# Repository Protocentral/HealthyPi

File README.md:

# This repository is OBSOLETE. Please visit https://github.com/Protocentral/protocentral-healthypi-v3 for the current version. 

# ProtoCentral HealthyPi HAT for Raspberry Pi

This HAT for Raspberry Pi 3 / 2 includes vital patient monitoring including ECG, respiration, pulse oximetry and features options to add blood pressure and body temperature sensing.

This is a one-of-a-kind, all-in-one HAT for your Raspberry Pi 2 /3 computer. Just plug it into the Raspberry Pi, install the graphical visualisation software and start using. Unlike available shields and breakouts that we carry for Arduino, this board combines all the functions into a a single board.

Repository Contents
-------------------
* **/firmware** - Atmel studio  and aduino example sketches.
* **/Hardware** - All Eagle design files (.brd, .sch)
* **/extras** - includes the datasheet
* **/gui** - HealthyPi GUI for Raspberry Pi and PC
* **/docs** - Additional Documentation

Getting Started (On Raspberry Pi):
----------------------------------

Mount ProtoCentral's Healthy PI Hat carefully onto the Raspberry Pi Board's GPIO Pins. And connect this setup with the Raspberry Pi's Display or HDMI Monitor. The Hat communicate with Raspberry Pi using UART interface. Connect the ECG electrodes and SPO2 Probe to the ProtoCentral's Healthy PI Hat.

It's now easy to get started with our brand-new installation script. Just follow the following steps on your Raspberry Pi.

To start, open up the terminal window (Menu -> Accessories -> Terminal) on Raspbian running on your Raspberry Pi:

In the terminal window, type the following lines. 

```bash
curl -sS http://pi.protocentral.com/pi.sh | sudo bash
```

It really is as simple as that !!

This code will install all the required overlays, configuration and application files to get the Healthy Pi up and running.

After the script reboots, you should be able to see the GUI display on the screen

### This completes the install!

If the above script does not work for you and would like to do a manual installation or would like to customize the code, check out [Advanced HealthyPi] (/docs/advanced-healthypi.md).

Using the HealthyPi GUI on Windows, MacOS and Linux
---------------------------------------------------
The HealthyPi board now streams the same data on the on-board USB port. This allows you to get the same data that goes to the Raspberry Pi, now on your desktop PC as well. 

Java 8 is required on all platforms for running the processing-based GUI application. You can download Java for your platform from the following link.

[https://java.com/en/download/](https://java.com/en/download/)

#### Installing drivers (only for Windows)

HealthyPi uses the same drivers as an Arduino Zero. Once plugged in to the USB port, the device would be recognized as an "Unknown Device". You can locate the device is the Windows Device Manager and manually install the drivers provided in the "drivers" folder in the Windows Executable ZIP archive provided.

MacOS and Linux do not need any drivers to be installed.

### Processing GUI Installation

Download the zip file containing the executable files from the following links for 32-bit/64-bit Windows. If you do not know if you have a 64-bit or 32-bit computer, please download the 32-bit version.

* [Windows 32-bit Executable (ZIP)](https://github.com/Protocentral/HealthyPi/releases/download/v0.2/healthypi_gui_win32.zip)
* [Windows 64-bit Executable (ZIP)](https://github.com/Protocentral/HealthyPi/releases/download/v0.2/healthypi_gui_win64.zip)
* [MacOS Executable (ZIP)](https://github.com/Protocentral/HealthyPi/releases/download/v0.2/healthypi_gui_macos.zip)
* [Linux 32-bit Executable (ZIP)](https://github.com/Protocentral/HealthyPi/releases/download/v0.2/healthypi_gui_linux32.zip)
* [Linux 64-bit Executable (ZIP)](https://github.com/Protocentral/HealthyPi/releases/download/v0.2/healthypi_gui_linux64.zip)

Simply download the appropriate file for your operating system, unzip the contents and run the executable program contained in it. 

Programming the on-board SAMD21 microcontroller
--------------------------------------------------

HealthyPi now supports programming using Arduino ! 

If you wish to program your own code on the HealthyPi board, check out [Modifying and recompiling HealthyPi Firmware](/docs/recompiling-firmware.md).

Connecting the ECG Electrodes
------------------------------
 A 3-electrode cable along with a standard stereo jack is provided along with the shield to connect the electrodes to the  board. 
 The other side of the electrode connector would connect to snap-on electrodes attached to the body. For testing purposes,    you can use an ECG simulator to provide inputs to the board. 

 Warning:
 When connecting the electodes to the body, it is safer to disconnect the mains power source to the Arduino. For example, if  you are using the Arduino along with a laptop, disconnecting the battery charger from the laptop would be a safe option.
 
Placing the Electrodes on the body
---------------------------------

License Information
===================

This product is open source! Both, our hardware and software are open source and licensed under the following licenses:

Hardware
---------

**All hardware is released under [Creative Commons Share-alike 4.0 International](http://creativecommons.org/licenses/by-sa/4.0/).**

Software
--------

**All software is released under the MIT License(http://opensource.org/licenses/MIT).**

Please check [*LICENSE.md*](LICENSE.md) for detailed license descriptions.

THE SOFTWARE IS PROVIDED "AS IS", WITHOUT WARRANTY OF ANY KIND, EXPRESS OR
IMPLIED, INCLUDING BUT NOT LIMITED TO THE WARRANTIES OF MERCHANTABILITY,
FITNESS FOR A PARTICULAR PURPOSE AND NONINFRINGEMENT. IN NO EVENT SHALL THE
AUTHORS OR COPYRIGHT HOLDERS BE LIABLE FOR ANY CLAIM, DAMAGES OR OTHER
LIABILITY, WHETHER IN AN ACTION OF CONTRACT, TORT OR OTHERWISE, ARISING FROM,
OUT OF OR IN CONNECTION WITH THE SOFTWARE OR THE USE OR OTHER DEALINGS IN THE
SOFTWARE.

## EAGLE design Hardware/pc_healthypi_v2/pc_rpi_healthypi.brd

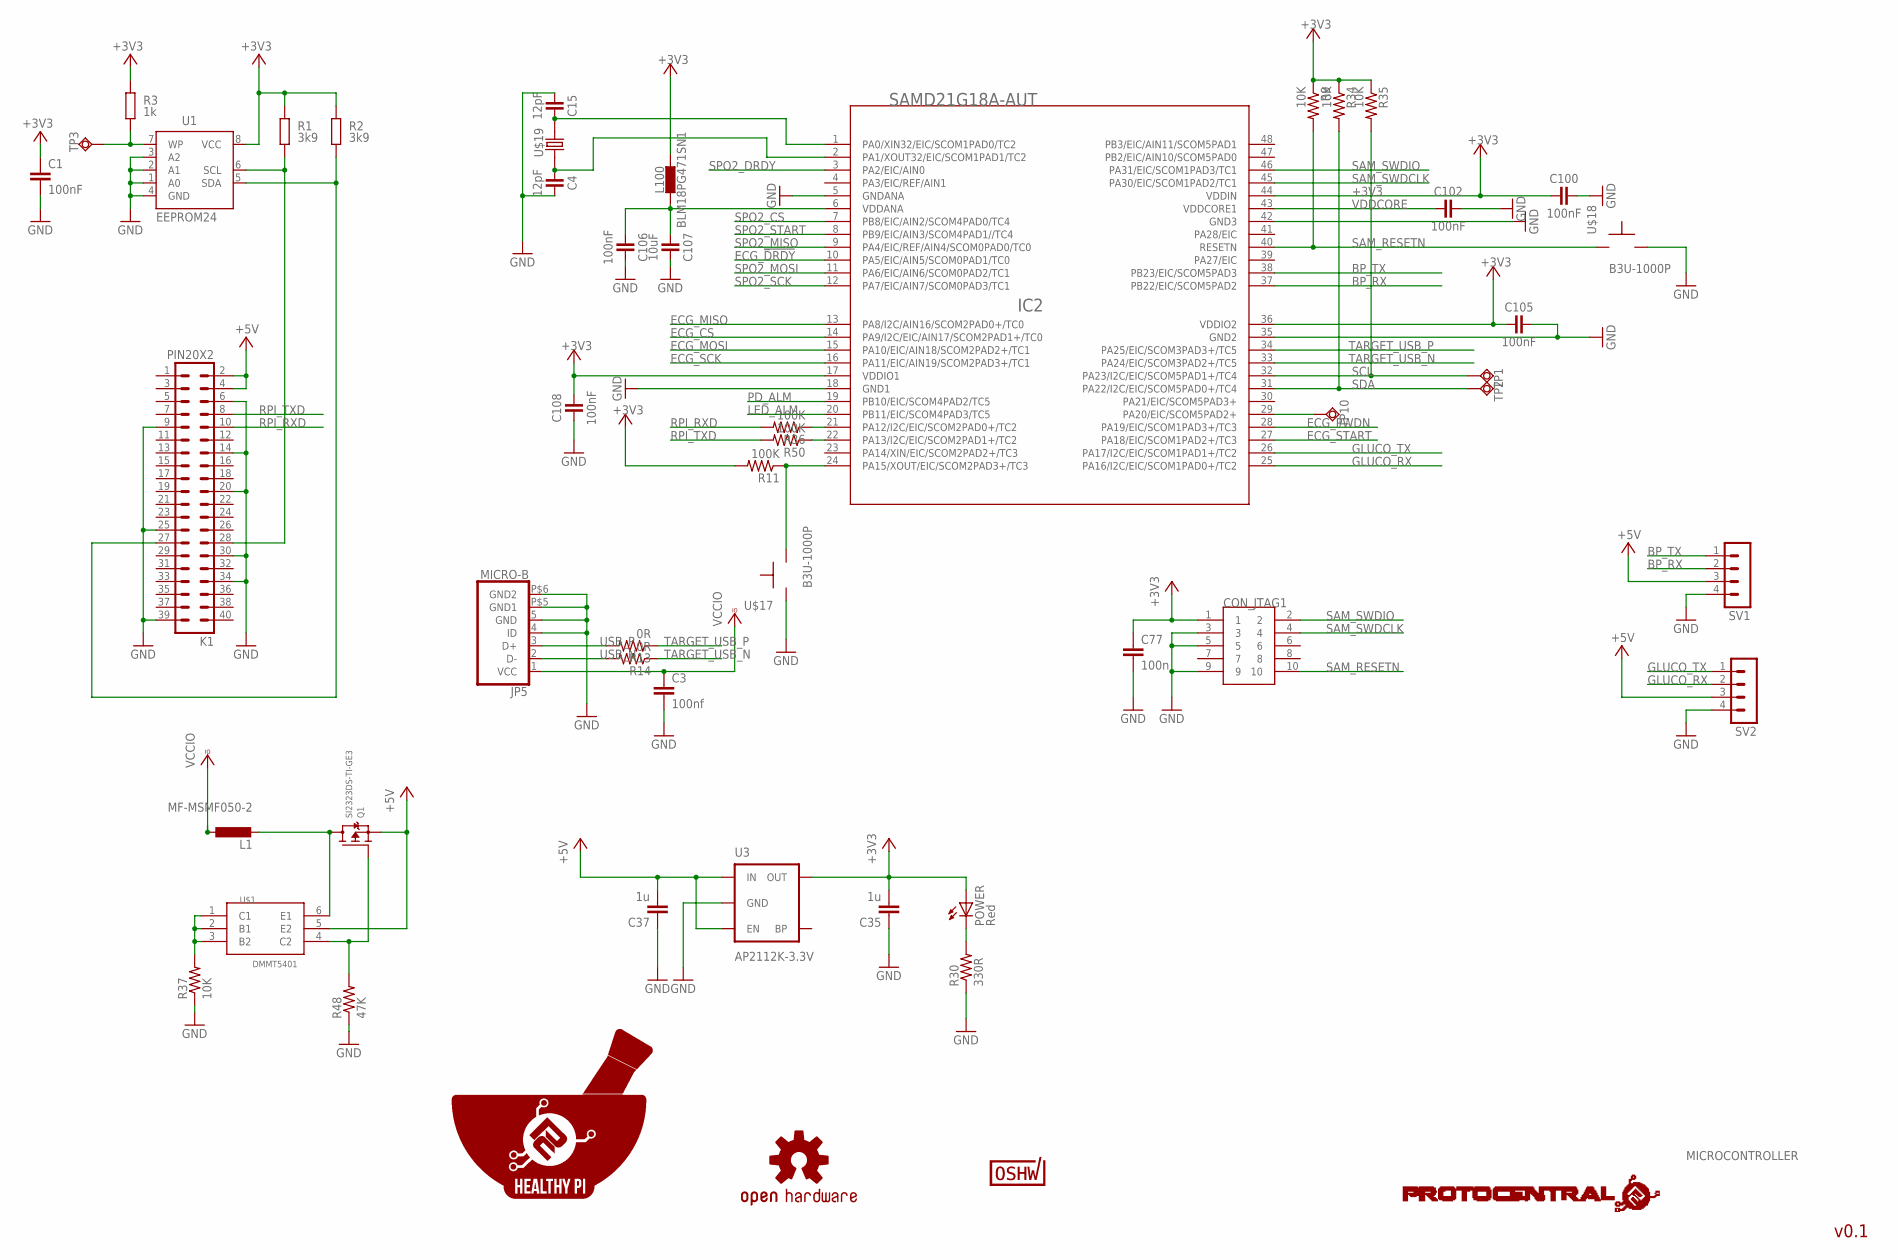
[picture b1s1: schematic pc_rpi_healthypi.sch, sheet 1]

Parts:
C1: 100nF; C0805K
C3: 100nf; C0402
C4, C15: 12pF; C0402
C35, C37: 1u; C0402
C77: 100n; C0805
C100, C102, C105, C106, C108: 100nF; C0805
C107: 10uF; C0805
CON_JTAG1: HDR-SMT-50MIL/5X2
IC2: SAMD21G18A-AUT; TQFP48
JP5: MICRO-B
K1: PIN20X2; PIN_20X2
L1: MF-MSMF050-2; L1812
L100: BLM18PG471SN1; C0603
POWER: Red; CHIPLED_0603
Q1: SI2323DS-TI-GE3; SOT23-R
R1, R2: 3k9; M0805; TOLERANCE 5%
R3: 1k; M0805; TOLERANCE 5%
R9, R34, R35, R37: 10K; R0805
R11: 100K; R0805
R13, R14: 0R; R0402
R30: 330R; R0402
R36, R50: 100K; R0402
R48: 47K; R0805
SV1, SV2: MA04-1
TP1, TP2, TP3, TP10: TPSQB1,27; B1,27
U1: EEPROM24; SOIC8
U3: AP2112K-3.3V; SOT23-5
U$1: DMMT5401; SOT26
U$5: OSHW-LOGOM; OSHW-LOGO-M
U$6: PROTY_LOGO_WITH_TEXT; PROTY_WITH_TEXT
U$13: CERT-SMALL; CERT-SMALL-SILK
U$15: HEALTHYPI
U$17, U$18: B3U-1000P
U$19: ECS-X-34B; ECX-31B

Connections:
+3V3: C1.1, C35.2, C77.1, C100.1, C105.1, C108.2, CON_JTAG1.1, IC2.17 (VDDIO1), IC2.36 (VDDIO2), IC2.44 (VDDIN), L100.2, POWER.A, R1.2, R2.2, R3.2, R9.1, R11.2, R34.1, R35.1, U1.8 (VCC), U3.5 (OUT); also elsewhere on the board
+5V: C37.2, K1.2, K1.4, Q1.2 (S), SV1.3, SV2.3, U3.1 (IN), U3.3 (EN), U$1.5 (E2)
BP_RX: IC2.37 (PB22/EIC/SCOM5PAD2), SV1.2
BP_TX: IC2.38 (PB23/EIC/SCOM5PAD3), SV1.1
ECG_!DRDY: IC2.10 (PA5/EIC/AIN5/SCOM0PAD1/TC0); also elsewhere on the board
ECG_CS: IC2.14 (PA9/I2C/EIC/AIN17/SCOM2PAD1+/TC0); also elsewhere on the board
ECG_MISO: IC2.13 (PA8/I2C/AIN16/SCOM2PAD0+/TC0); also elsewhere on the board
ECG_MOSI: IC2.15 (PA10/EIC/AIN18/SCOM2PAD2+/TC1); also elsewhere on the board
ECG_PWDN: IC2.28 (PA19/EIC/SCOM1PAD3+/TC3); also elsewhere on the board
ECG_SCK: IC2.16 (PA11/EIC/AIN19/SCOM2PAD3+/TC1); also elsewhere on the board
ECG_START: IC2.27 (PA18/EIC/SCOM1PAD2+/TC3); also elsewhere on the board
GLUCO_RX: IC2.25 (PA16/I2C/EIC/SCOM1PAD0+/TC2), SV2.2
GLUCO_TX: IC2.26 (PA17/I2C/EIC/SCOM1PAD1+/TC2), SV2.1
GND: C1.2, C3.2, C4.2, C15.1, C35.1, C37.1, C77.2, C100.2, C102.2, C105.2, C106.2, C107.2, C108.1, CON_JTAG1.3, CON_JTAG1.5, CON_JTAG1.9, IC2.5 (GNDANA), IC2.18 (GND1), IC2.35 (GND2), IC2.42 (GND3), JP5.4 (ID), JP5.5 (GND), JP5.P$5 (GND1), JP5.P$6 (GND2), K1.6, K1.9, K1.14, K1.20, K1.25, K1.30, K1.34, K1.39, R30.1, R37.1, R48.1, SV1.4, SV2.4, U1.1 (A0), U1.2 (A1), U1.3 (A2), U1.4 (GND), U3.2 (GND), U$17.P$1, U$18.P$2; also elsewhere on the board
LED_ALM: IC2.20 (PB11/EIC/SCOM4PAD3/TC5); also elsewhere on the board
unnamed: K1.28, R1.1, U1.6 (SCL)
unnamed: K1.27, R2.1, U1.5 (SDA)
unnamed: R3.1, TP3.TP, U1.7 (WP)
unnamed: C15.2, IC2.1 (PA0/XIN32/EIC/SCOM1PAD0/TC2), U$19.P$2 (2)
unnamed: C106.1, C107.1, IC2.6 (VDDANA), L100.1
unnamed: POWER.C, R30.2
unnamed: C4.1, IC2.2 (PA1/XOUT32/EIC/SCOM1PAD1/TC2), U$19.P$1 (1)
unnamed: IC2.21 (PA12/I2C/EIC/SCOM2PAD0+/TC2), R36.1
unnamed: IC2.22 (PA13/I2C/EIC/SCOM2PAD1+/TC2), R50.1
unnamed: IC2.24 (PA15/XOUT/EIC/SCOM2PAD3+/TC3), R11.1, U$17.P$2
unnamed: IC2.29 (PA20/EIC/SCOM5PAD2+), TP10.TP
unnamed: R37.2, U$1.1 (C1), U$1.2 (B1), U$1.3 (B2)
unnamed: Q1.1 (G), R48.2, U$1.4 (C2)
unnamed: L1.2, Q1.3 (D), U$1.6 (E1)
PD_ALM: IC2.19 (PB10/EIC/SCOM4PAD2/TC5); also elsewhere on the board
RPI_RXD: K1.10, R36.2
RPI_TXD: K1.8, R50.2
SAM_RESETN: CON_JTAG1.10, IC2.40 (RESETN), R9.2, U$18.P$1
SAM_SWDCLK: CON_JTAG1.4, IC2.45 (PA30/EIC/SCOM1PAD2/TC1)
SAM_SWDIO: CON_JTAG1.2, IC2.46 (PA31/EIC/SCOM1PAD3/TC1)
SCL: IC2.32 (PA23/I2C/EIC/SCOM5PAD1+/TC4), R35.2, TP1.TP
SDA: IC2.31 (PA22/I2C/EIC/SCOM5PAD0+/TC4), R34.2, TP2.TP
SPO2_CS: IC2.7 (PB8/EIC/AIN2/SCOM4PAD0/TC4); also elsewhere on the board
SPO2_DRDY: IC2.3 (PA2/EIC/AIN0); also elsewhere on the board
SPO2_MISO: IC2.9 (PA4/EIC/REF/AIN4/SCOM0PAD0/TC0); also elsewhere on the board
SPO2_MOSI: IC2.11 (PA6/EIC/AIN6/SCOM0PAD2/TC1); also elsewhere on the board
SPO2_SCK: IC2.12 (PA7/EIC/AIN7/SCOM0PAD3/TC1); also elsewhere on the board
SPO2_START: IC2.8 (PB9/EIC/AIN3/SCOM4PAD1//TC4); also elsewhere on the board
TARGET_USB_N: IC2.33 (PA24/EIC/SCOM3PAD2+/TC5), R14.1
TARGET_USB_P: IC2.34 (PA25/EIC/SCOM3PAD3+/TC5), R13.1
USB_N: JP5.2 (D-), R14.2
USB_P: JP5.3 (D+), R13.2
VCCIO: C3.1, JP5.1 (VCC), L1.1
VDDCORE: C102.1, IC2.43 (VDDCORE1)

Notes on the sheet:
v0.1
MICROCONTROLLER

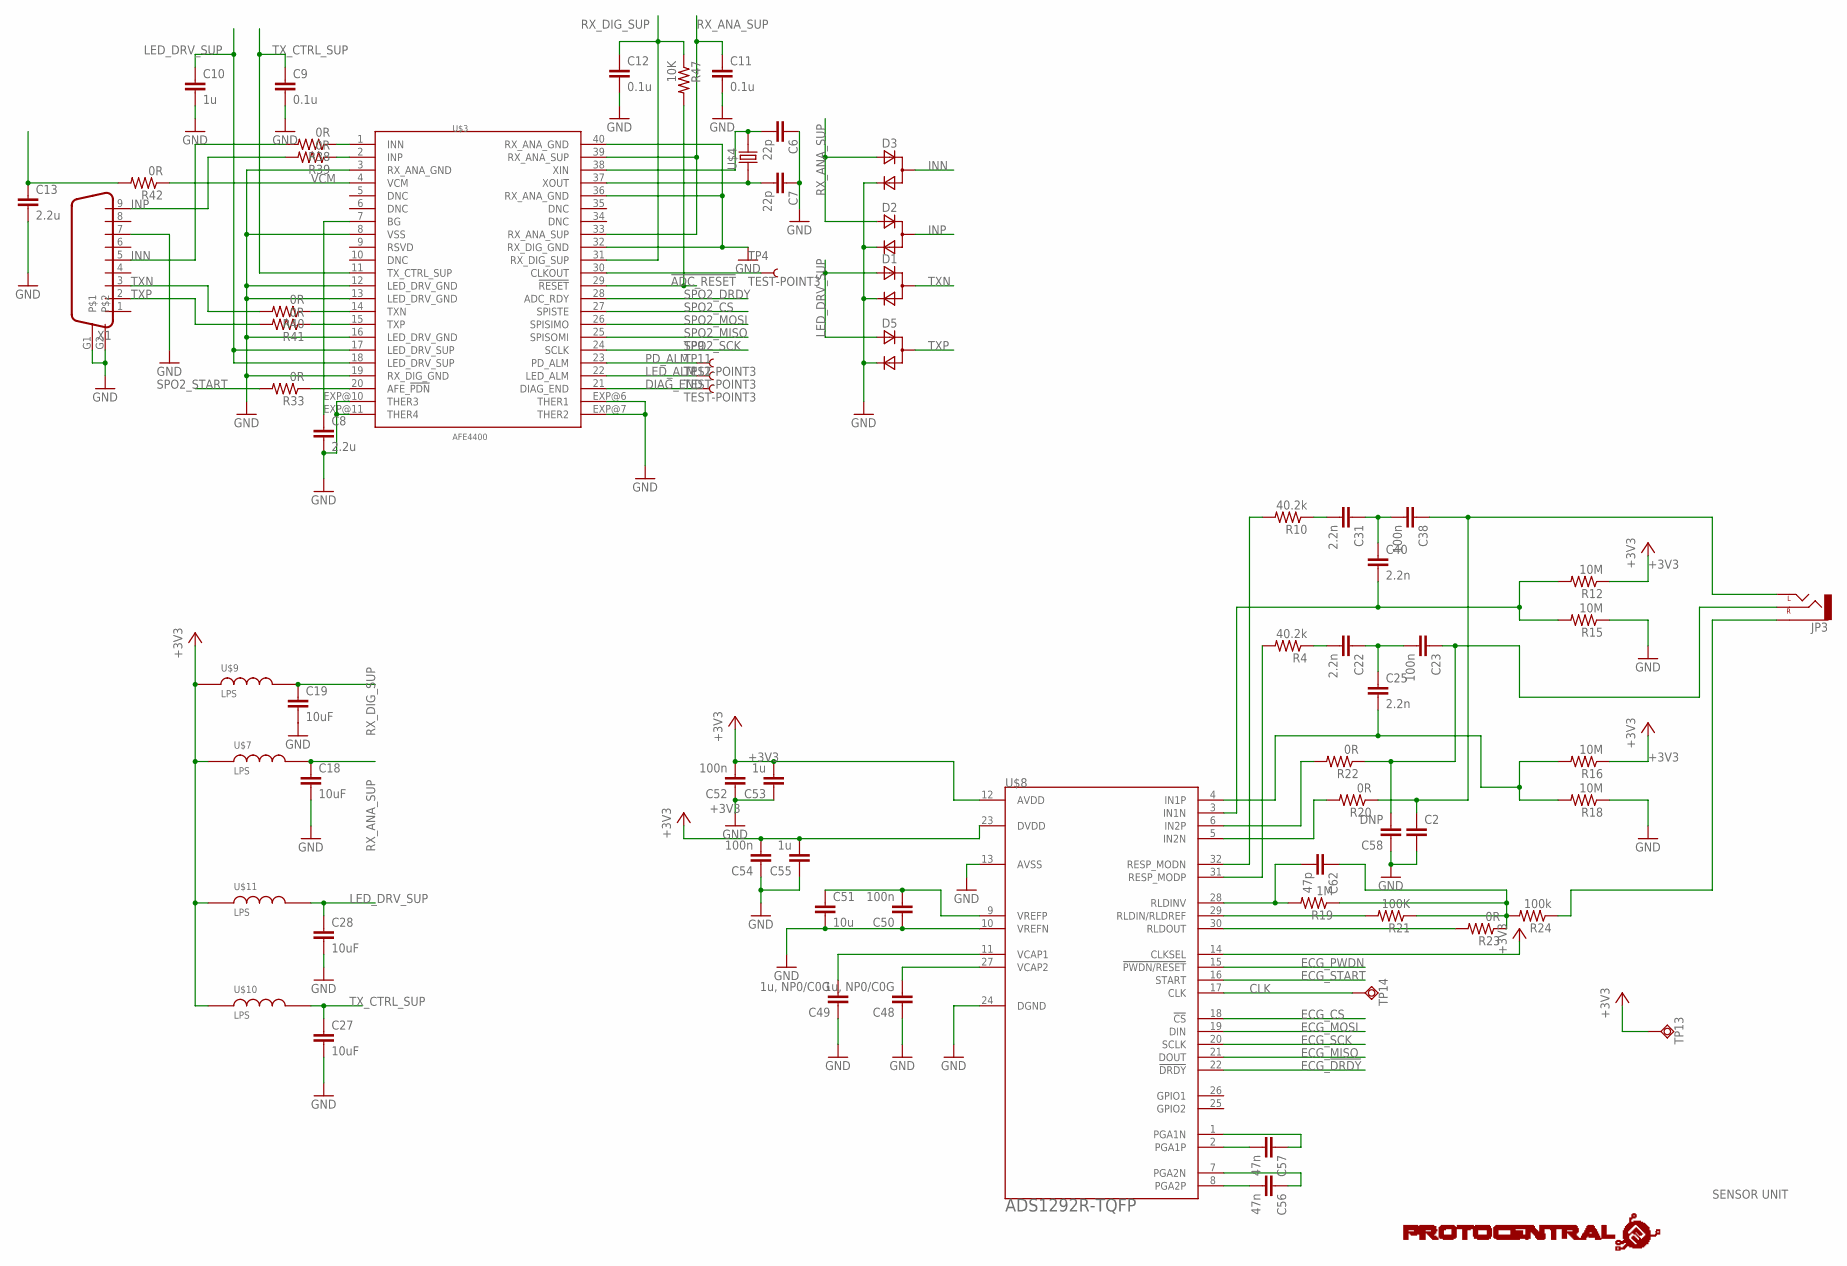
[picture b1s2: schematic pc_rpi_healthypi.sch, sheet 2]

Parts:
C2: C-EUC0402; C0402
C6, C7: 22p; C0402
C8, C13: 2.2u; C0402
C9, C11, C12: 0.1u; C0402
C10: 1u; C0805
C18, C19, C27, C28: 10uF; C0805
C22, C25, C31, C40: 2.2n; C0402
C23, C38, C50, C52, C54: 100n; C0402
C48, C49: 1u, NP0/C0G; C0402
C51: 10u; C0603
C53, C55: 1u; C0402
C56, C57: 47n; C0402
C58: DNP; C0402
C62: 47p; C0402
D1, D2, D3, D5: D_ACACSOT323; SOT323
JP3: AUDIO-JACKSMD2; AUDIO-JACK-3.5MM-SMD
R4, R10: 40.2k; R0402
R12, R15, R16, R18: 10M; R0402
R19: 1M; R0402
R20, R22, R23, R33, R38, R39, R40, R41, R42: 0R; R0402
R21: 100K; R0402
R24: 100k; R0402
R47: 10K; R0402
TP4, TP9, TP11, TP12: TEST-POINT3; PAD.03X.03
TP13, TP14: TPSQB1,27; B1,27
U$2: PROTY_LOGO_WITH_TEXT; PROTY_WITH_TEXT
U$3: AFE4400; QFN-40
U$4: ABM3
U$7, U$9, U$10, U$11: LPS
U$8: ADS1292R-TQFP; SQFP-S-5X5-32
X1: DB9

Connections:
!ADC_RESET: R47.2, U$3.29 (!RESET)
+3V3: C52.2, C53.2, C54.2, C55.2, R12.1, R16.1, TP13.TP, U$7.1, U$8.12 (AVDD), U$8.14 (CLKSEL), U$8.23 (DVDD), U$9.1, U$10.1, U$11.1; also elsewhere on the board
CLK: TP14.TP, U$8.17 (CLK)
DIAG_END: TP12.P$1, U$3.21 (DIAG_END)
ECG_!DRDY: U$8.22 (!DRDY); also elsewhere on the board
ECG_CS: U$8.18 (!CS); also elsewhere on the board
ECG_MISO: U$8.21 (DOUT); also elsewhere on the board
ECG_MOSI: U$8.19 (DIN); also elsewhere on the board
ECG_PWDN: U$8.15 (!PWDN/RESET); also elsewhere on the board
ECG_SCK: U$8.20 (SCLK); also elsewhere on the board
ECG_START: U$8.16 (START); also elsewhere on the board
GND: C2.2, C6.1, C7.1, C8.2, C9.2, C10.2, C11.2, C12.2, C13.2, C18.2, C19.2, C27.2, C28.2, C48.1, C49.1, C50.1, C51.2, C52.1, C53.1, C54.1, C55.1, C58.1, D1.2 (C), D2.2 (C), D3.2 (C), D5.2 (C), R15.1, R18.1, U$3.3 (RX_ANA_GND), U$3.8 (VSS), U$3.12 (LED_DRV_GND), U$3.13 (LED_DRV_GND), U$3.16 (LED_DRV_GND), U$3.19 (RX_DIG_GND), U$3.32 (RX_DIG_GND), U$3.36 (RX_ANA_GND), U$3.40 (RX_ANA_GND), U$3.EXP@6 (THER1), U$3.EXP@7 (THER2), U$3.EXP@10 (THER3), U$3.EXP@11 (THER4), U$8.10 (VREFN), U$8.13 (AVSS), U$8.24 (DGND), X1.7, X1.G1, X1.G2; also elsewhere on the board
INN: D3.1 (CA), R38.2, X1.5
INP: D2.1 (CA), R39.2, X1.9
LED_ALM: TP11.P$1, U$3.22 (LED_ALM); also elsewhere on the board
LED_DRV_SUP: C10.1, C28.1, D1.3 (A), D5.3 (A), U$3.17 (LED_DRV_SUP), U$3.18 (LED_DRV_SUP), U$11.2
unnamed: R4.2, U$8.31 (RESP_MODP)
unnamed: C6.2, U$3.38 (XIN), U$4.2
unnamed: C22.2, R4.1
unnamed: C22.1, C23.2, C25.1
unnamed: R22.2, U$8.6 (IN2P)
unnamed: C7.2, U$3.37 (XOUT), U$4.1
unnamed: R20.2, U$8.5 (IN2N)
unnamed: C8.1, U$3.7 (BG)
unnamed: TP4.P$1, U$3.30 (CLKOUT)
unnamed: R38.1, U$3.1 (INN)
unnamed: R39.1, U$3.2 (INP)
unnamed: C48.2, U$8.27 (VCAP2)
unnamed: R40.1, U$3.14 (TXN)
unnamed: R41.1, U$3.15 (TXP)
unnamed: C13.1, R42.2
unnamed: R10.2, U$8.32 (RESP_MODN)
unnamed: C31.2, R10.1
unnamed: C31.1, C38.2, C40.1
unnamed: C2.1, C38.1, JP3.TIP (LEFT), R20.1
unnamed: C40.2, R12.2, R15.2, U$8.3 (IN1N)
unnamed: C25.2, R16.2, R18.2, U$8.4 (IN1P)
unnamed: R21.2, U$8.29 (RLDIN/RLDREF)
unnamed: C62.2, R19.2, U$8.28 (RLDINV)
unnamed: C62.1, R19.1, R21.1, R23.1, R24.2
unnamed: C49.2, U$8.11 (VCAP1)
unnamed: C56.2, U$8.8 (PGA2P)
unnamed: C56.1, U$8.7 (PGA2N)
unnamed: C50.2, C51.1, U$8.9 (VREFP)
unnamed: C57.2, U$8.2 (PGA1P)
unnamed: C57.1, U$8.1 (PGA1N)
unnamed: C23.1, C58.2, JP3.RING (RIGHT), R22.1
unnamed: R23.2, U$8.30 (RLDOUT)
unnamed: JP3.SLEEVE, R24.1
unnamed: R33.1, U$3.20 (AFE_!PDN)
PD_ALM: TP9.P$1, U$3.23 (PD_ALM); also elsewhere on the board
RX_ANA_SUP: C11.1, C18.1, D2.3 (A), D3.3 (A), U$3.33 (RX_ANA_SUP), U$3.39 (RX_ANA_SUP), U$7.2
RX_DIG_SUP: C12.1, C19.1, R47.1, U$3.31 (RX_DIG_SUP), U$9.2
SPO2_CS: U$3.27 (SPISTE); also elsewhere on the board
SPO2_DRDY: U$3.28 (ADC_RDY); also elsewhere on the board
SPO2_MISO: U$3.25 (SPISOMI); also elsewhere on the board
SPO2_MOSI: U$3.26 (SPISIMO); also elsewhere on the board
SPO2_SCK: U$3.24 (SCLK); also elsewhere on the board
SPO2_START: R33.2; also elsewhere on the board
TXN: D1.1 (CA), R40.2, X1.3
TXP: D5.1 (CA), R41.2, X1.2
TX_CTRL_SUP: C9.1, C27.1, U$3.11 (TX_CTRL_SUP), U$10.2
VCM: R42.1, U$3.4 (VCM)

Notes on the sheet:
SENSOR UNIT

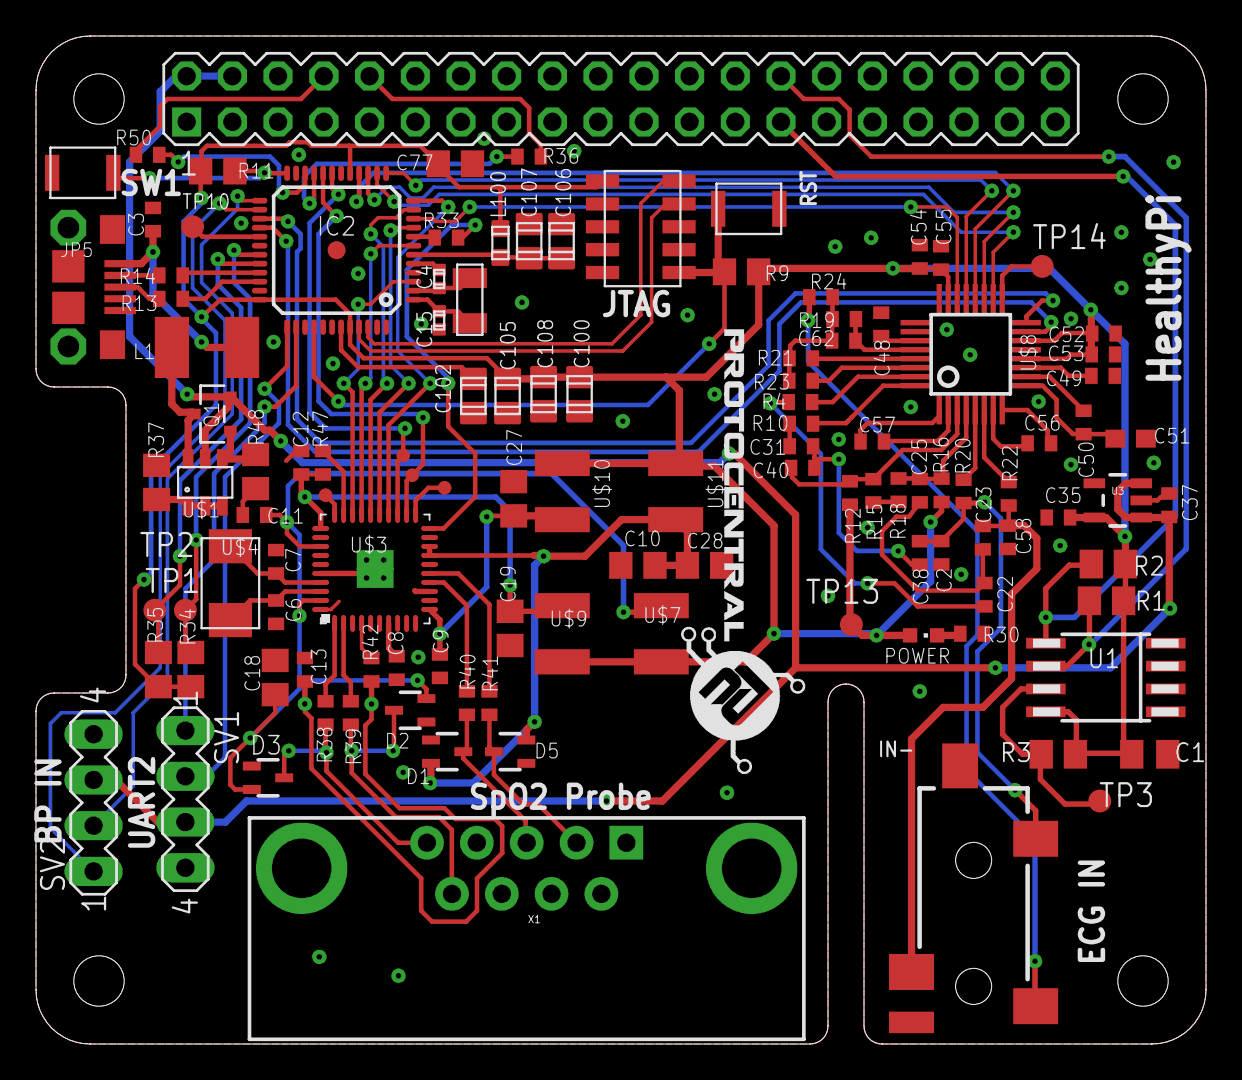
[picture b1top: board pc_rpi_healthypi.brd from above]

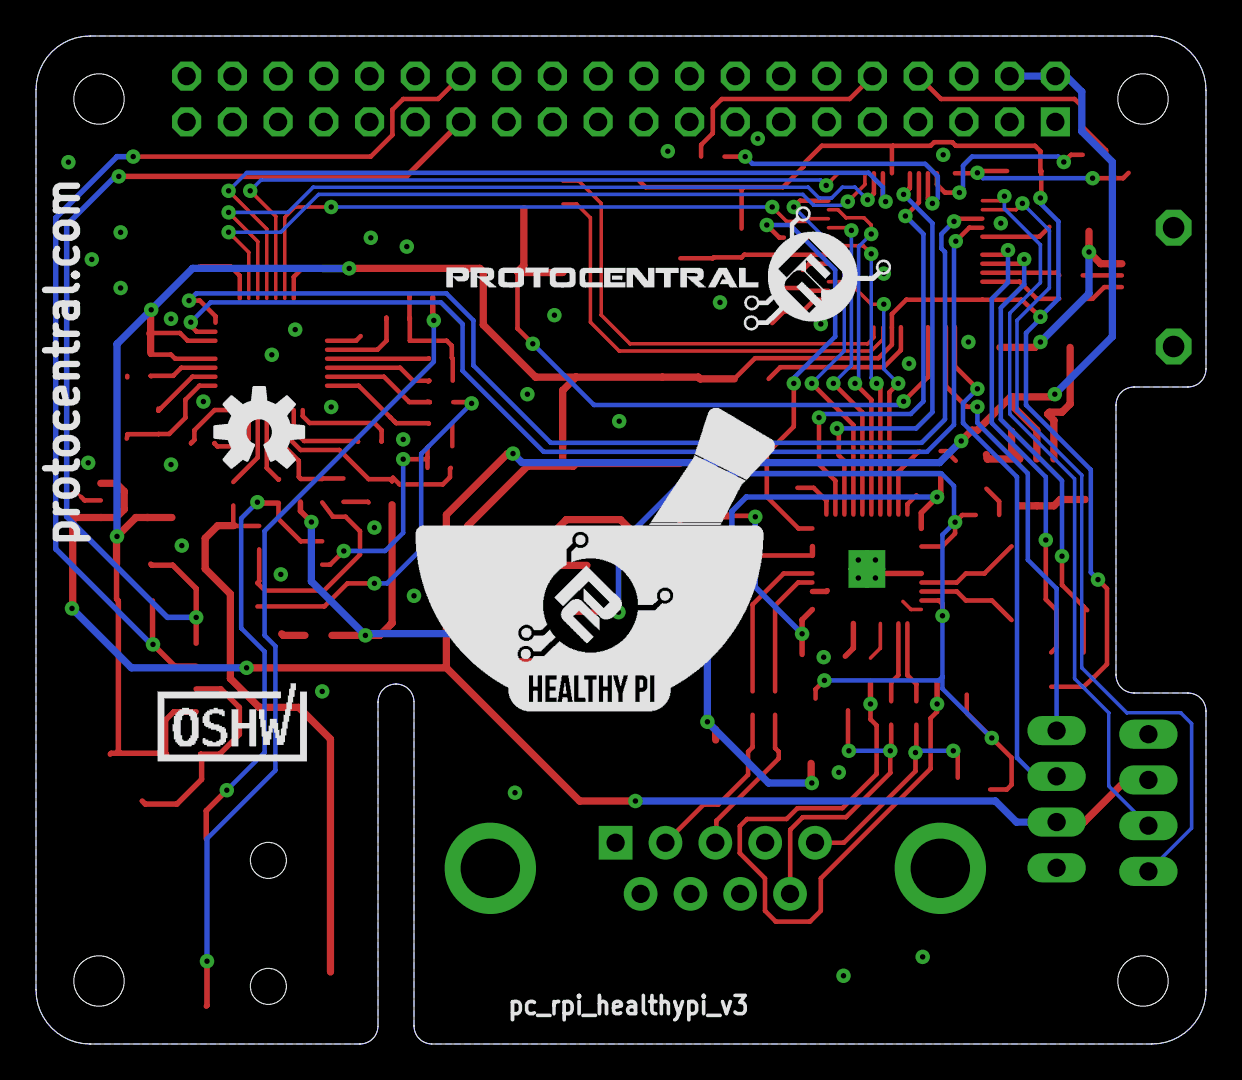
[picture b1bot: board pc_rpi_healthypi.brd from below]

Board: 4 copper layers, 65.0 x 56.0 mm, 121 parts (4 on the bottom side), 95 nets.

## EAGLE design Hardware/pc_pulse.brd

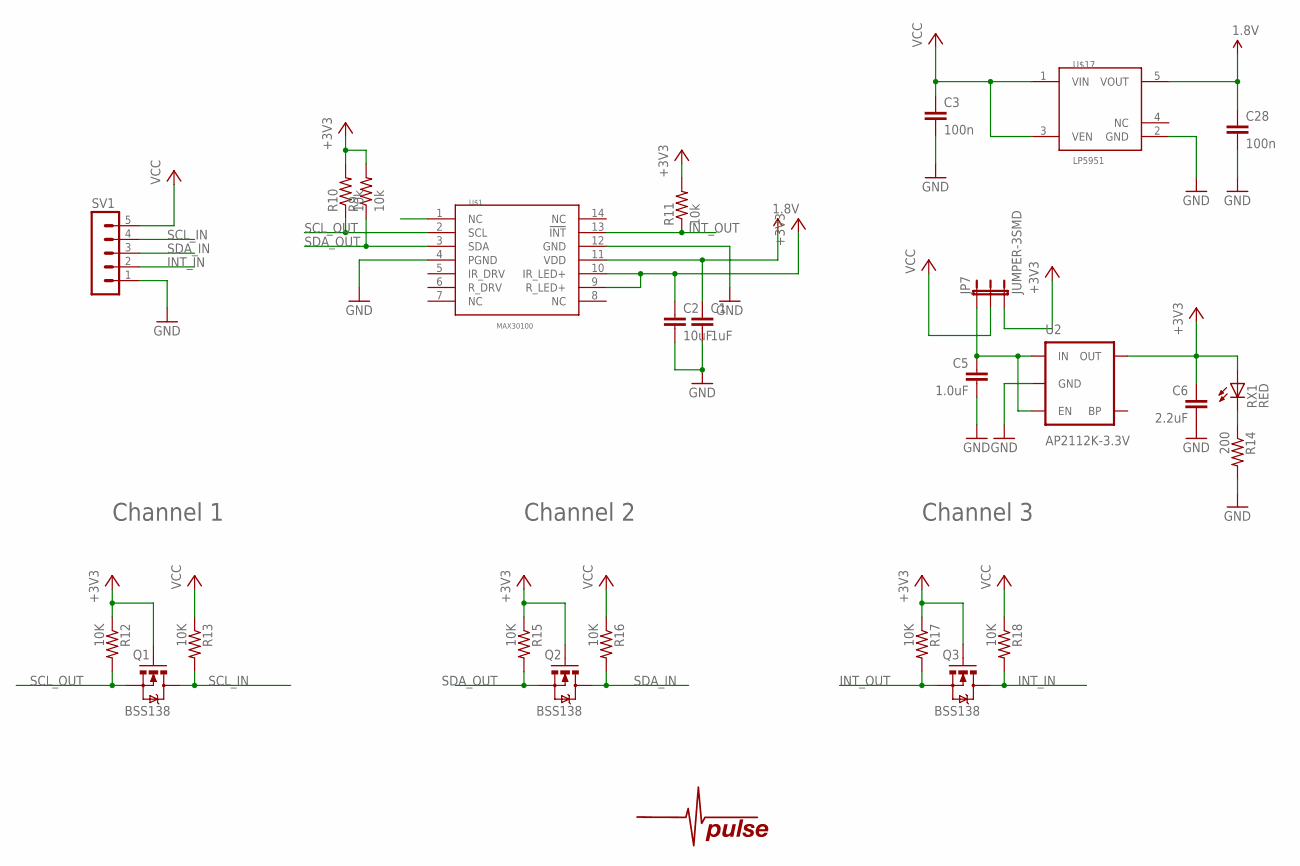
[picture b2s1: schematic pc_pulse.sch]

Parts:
C1: 1uF; C0805
C2: 10uF; C0805
C3, C28: 100n; C0402
C5: 1.0uF; 0805
C6: 2.2uF; C0805
JP7: JUMPER-3SMD; SJ_3
Q1, Q2, Q3: BSS138; SOT23-3
R9, R10, R11: 10k; R0402
R12, R13, R15, R16, R17, R18: 10K; 0402-RES
R14: 200; R0402
RX1: RED; CHIPLED_0603
SV1: MA05-1
U2: AP2112K-3.3V; SOT23-5
U$1: MAX30100; OESIP-14
U$3: PROTY_LOGO_WITH_TEXT; PROTY_WITH_TEXT
U$4: PULSE
U$17: LP5951; SC70-5

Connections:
1.8V: C1.1, C28.1, U$1.11 (VDD), U$17.5 (VOUT)
+3V3: C2.1, C6.1, JP7.3, Q1.1 (G), Q2.1 (G), Q3.1 (G), R9.2, R10.2, R11.2, R12.1, R15.1, R17.1, RX1.A, U2.5 (OUT), U$1.9 (R_LED+), U$1.10 (IR_LED+)
GND: C1.2, C2.2, C3.2, C5.2, C6.2, C28.2, R14.2, SV1.1, U2.2 (GND), U$1.4 (PGND), U$1.12 (GND), U$17.2 (GND)
INT_IN: Q3.3 (D), R18.2, SV1.2
INT_OUT: Q3.2 (S), R11.1, R17.2, U$1.13 (!INT)
unnamed: C5.1, JP7.1, U2.1 (IN), U2.3 (EN)
unnamed: R14.1, RX1.C
SCL_IN: Q1.3 (D), R13.2, SV1.4
SCL_OUT: Q1.2 (S), R10.1, R12.2, U$1.2 (SCL)
SDA_IN: Q2.3 (D), R16.2, SV1.3
SDA_OUT: Q2.2 (S), R9.1, R15.2, U$1.3 (SDA)
VCC: C3.1, JP7.2, R13.1, R16.1, R18.1, SV1.5, U$17.1 (VIN), U$17.3 (VEN)

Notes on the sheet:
Channel 1
Channel 2
Channel 3

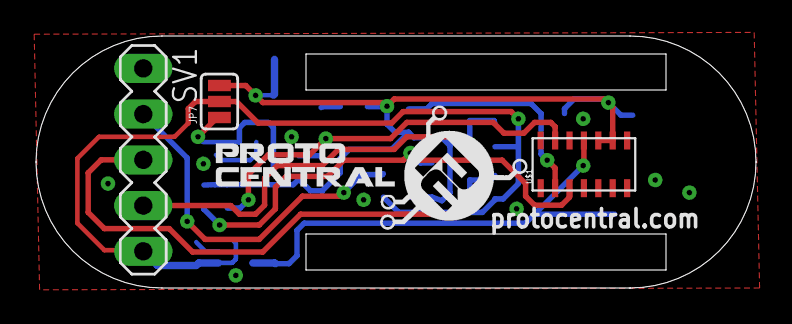
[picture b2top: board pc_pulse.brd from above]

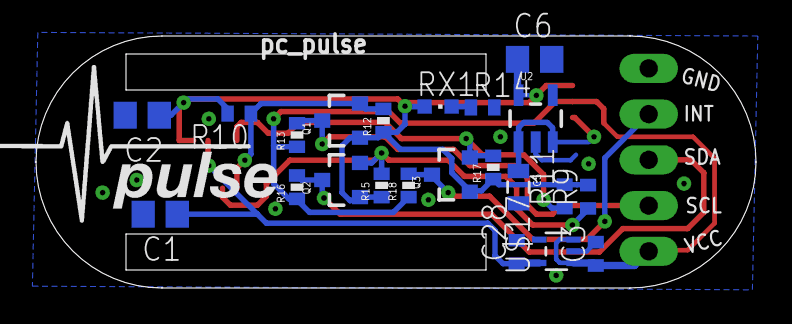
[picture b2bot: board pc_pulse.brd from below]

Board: 4 copper layers, 40.0 x 14.0 mm, 27 parts (23 on the bottom side), 12 nets.

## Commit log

2016-09-30 Raspberry Pi Configured Code
2016-09-30 PC Configured Code
2016-09-30 Final Output
2016-09-30 Readme
2016-09-30 PC Output
2016-09-30 Raspberry Pi Output
2016-10-03 Serial Enable
2016-10-05 Images
2016-10-05 Processing
2016-10-27 PC Configured Code Using Processing
2016-10-27 Processing Code
2016-10-27 Libraries
2016-10-27 Processing Output
2016-10-27 RPi Configured Code
2017-01-20 Updated HealthyPi v2 schematics
2017-01-20 Cleaned up folder structure for code
2017-01-20 Updated gui folder name
2017-01-20 Updated read and images
2017-02-04 Added install script test
2017-02-04 shell test
2017-02-04 script
2017-02-04 Edit Readme, add docs folder
2017-02-04 Edit Readme
2017-02-07 Uploaded binary files
2017-02-08 Updated folder structure
2017-02-09 Updated Readme to new script based installation
2017-02-09 Updated docs
2017-02-12 Updated License Information
2017-02-12 Updated images and directory structure
2017-02-16 Added HealthyPi Arduino Support
2017-02-16 Added Win32 and Win64 standalone supprot
2017-02-20 updated image
2017-02-22 Updated application binaries
2017-02-24 Added support and documentation for Windows, Linux and MacOS
2017-02-24 Set theme jekyll-theme-cayman
2017-02-24 Added gitignore
2017-02-24 Updated Gitignore
2017-02-24 Updated remove binaries
2017-02-24 Removed drivers from source
2017-02-27 Add Gplot library for plotting
2017-03-06 Set theme jekyll-theme-architect
2017-03-06 Set theme jekyll-theme-tactile
2017-03-10 add waffle.io badge
2017-03-13 Added Grafica library for pltos
2017-03-13 Removed all ignored files
2017-03-13 Removed binary files
2017-04-30 Added new HealthyPi v3 GUI
2017-04-30 Added HealthyPi v3 Schematics
2017-05-06 Docs: Fixed broken header in README
2017-05-06 Docs: Fixed broken header
2018-01-06 fixes image with spaces
    > image does not get rendered.

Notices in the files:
README.md:
CC-BY-SA-4.0
parts and their libraries:
SparkFun-Connectors: Licensing: Creative Commons ShareAlike 4.0 International - https://creativecommons.org/licenses/by-sa/4.0
